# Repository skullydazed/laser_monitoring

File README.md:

Device For Monitoring Some Critical Parameters of a CO2 Laser Cutter.
=====================================================================

This is a project undertaken by members of Idea Fab Labs in Santa Cruz to
help monitor some critical parameters of our laser cutter. We're using
this to monitor 6 different parameters on our Redsail 100w Laser Cutter:

* Overall AC current usage (as measured at the electrical panel's "In")
* Chiller AC current usage
* AC in to power supply
* DC out of power supply
* Temperature at the tube's water inlet
* Temperature at the tube's water outlet

Who Built This?
---------------

This project was created by [Zach White](https://github.com/skullydazed) with
significant contributions from Ben Hencke ([github](https://github.com/simap),
[website](http://www.bhencke.com)), Austin Neff, and Chris Maddox.
Many other members at Idea Fab Labs contributed ideas and suggestions in
the process of building this.

Special thanks to Kelsey Rice, the Laser Zone Manager, for being open to this
crazy idea and lending his support.

Repository Contents
===================

Arduino Shield
--------------

* [doc/Arduino Shield Gerbers](doc/Arduino Shield Gerbers) - This directory
  contains gerbers for the Arduino Shield.
* [doc/Arduino Shield Schematic.png](doc/Arduino Shield Schematic.png) - The
  schematic for hooking up the sensors to the Arduino.
* [CAD/Laser Monitor.brd](Laser Monitor.brd) and
  [CAD/Laser Monitor.sch](Laser Monitor.sch) - EAGLE files for the Arduino
  Shield

Raspberry Pi
------------

* [CAD/Laser Cut Case.dxf](CAD/Laser Cut Case.dxf) - Plans for a case that
  can contain the Raspberry Pi

Software
--------

* [Laser_Monitoring.ino](Laser_Monitoring.ino) - Arduino sketch for reading
  and reporting data over serial
* [laserd](laserd) - Python 3.4 script to fetch readings and shove
  them into an RRD
* [laser_lcd](laser_lcd) - Python 3.4 script to fetch readings from RRD and
  display them on a PiFace Control and Display board

Required Parts
==============

* 1 &times; Computer with USB able to run python 3.4
* 1 &times; [Arduino](http://store-usa.arduino.cc/products/a000066) (we used
  an Uno, but any arduino with analog pins will work.)
* 3 &times; [50A Current sensors](http://www.robotshop.com/en/dfrobot-50a-current-sensor-ac-dc.html)
* 2 &times; [LM34DZ Fahrenheit Temperature Sensor](http://www.allelectronics.com/make-a-store/item/lm34dz/fahrenheit-temperature-sensor/1.html)

Optional Parts
--------------

These parts aren't required for the monitoring portion, but we found each one
to be a valuable addition to our implementation.

* 1 &times; [Raspberry Pi](https://www.raspberrypi.org)
* 1 &times; [PiFace Control and Display Board](https://www.element14.com/community/docs/DOC-55622/l/piface-control-and-display-board-for-use-with-raspberry-pi)
* 1 &times; USB Wifi Adaptor
* 1 &times; [Custom Arduino Shield](Laser Monitor.brd) - etch it yourself or
  have it made
* 6 &times; 10k resistors
* 1 &times; [Varistor](http://www.mouser.com/search/ProductDetail.aspx?R=0virtualkey0virtualkeyV8ZA2P) for overload protection
* 1 &times; Laser cut case. See [Laser Cut Case.dxf](Laser Cut Case.dxf) for
  plans. Use any 3mm (1/8") material.
* 24 &times; M3 x 10 Screw + Nut

Assembly
========

Program The Arduino
-------------------

(You can do this part on any computer, it doesn't have to be the monitoring
computer.)

1. Open the [Laser_Monitoring.ino](Laser_Monitoring.ino) file in the Arduino
   IDE
2. Upload the sketch to the Arduino
3. Open up the Serial Monitor (Tools -> Serial Monitor)
4. You should see a line written once a second consisting of 6 tab separated
   numbers
5. Close the Arduino IDE

Wiring
------

Start by wiring up your Arduino. If you have made the PCB, you only need to
plug the current sensors in, wire up the temp sensors, and interface with the
laser's power supply for DC current. If you decide to forego the PCB you
will need to reference [the schematic](doc/Arduino Shield Schematic.png) to get
everything wired up properly.

You will need to make your own pigtails for the temperature sensors. For
consistency with the current sensors we recommend using Red for VCC, Blue for
Signal, and Black for GND.

FIXME: Have Ben describe connecting the DC current sensing.

Once you've wired up the Arduino, you can plug it into the monitoring computer
(in our setup that's the Raspberry Pi)

Setup and First Run
===================

* Clone this repository to /home/pi/Laser_Monitor
* Create the RRD file:
  * `rrdtool create readings.rrd --step 1 \`  
    `DS:current1:GAUGE:30:U:U \`  
    `DS:current2:GAUGE:30:U:U \`  
    `DS:current3:GAUGE:30:U:U \`  
    `DS:dc_current:GAUGE:30:U:U \`  
    `DS:temp1:GAUGE:30:U:U \`  
    `DS:temp2:GAUGE:30:U:U \`  
    `RRA:AVERAGE:0.5:1:24 RRA:AVERAGE:0.5:6:10`
* Run `laserd` to read data from the Arduino and write it to an RRD file.
* Run `laser_lcd` to read data from the RRD and write it to the LCD.

Systemd
=======

If you're using a systemd based distribution you can use
[setup_systemd.sh](setup_systemd.sh) to setup the RRD file and the services
that will write to and read from that RRD.

TODO
====

* Create a web interface to display data from the RRD

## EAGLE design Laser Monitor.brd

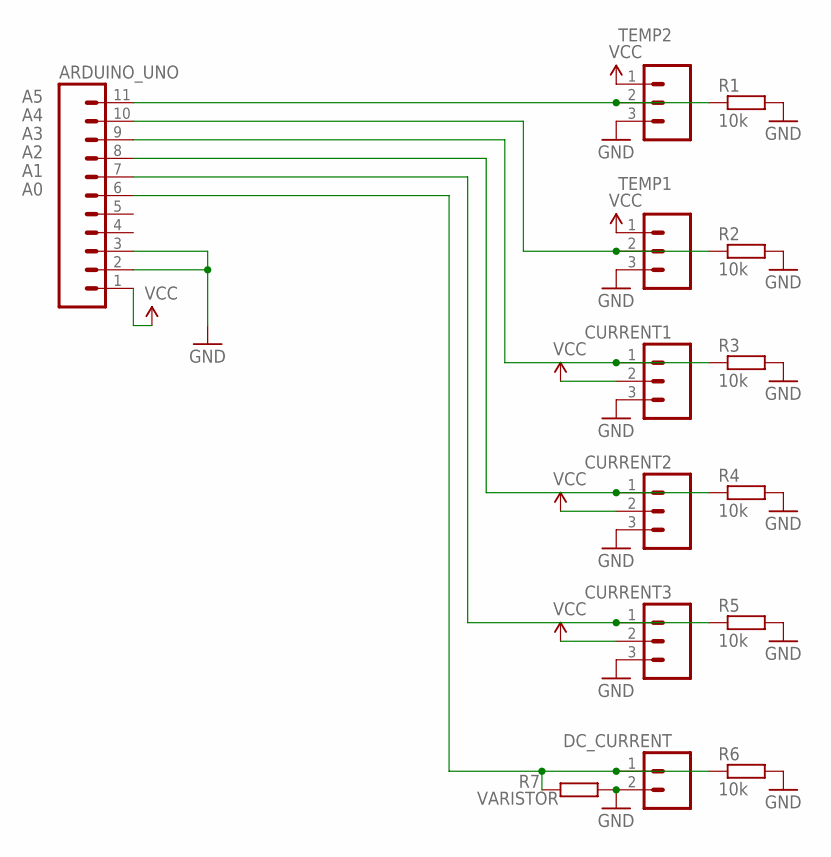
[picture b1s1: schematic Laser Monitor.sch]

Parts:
ARDUINO_UNO: M11PTH; 1X11
CURRENT1, CURRENT2, CURRENT3: M03PTH; 1X03
DC_CURRENT: M02PTH; 1X02
R1, R2, R3, R4, R5, R6: 10k; 0204V
R7: VARISTOR; P0817V
TEMP1, TEMP2: M03PTH; 1X03

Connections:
A0: ARDUINO_UNO.6, DC_CURRENT.1, R6.1, R7.2
A1: ARDUINO_UNO.7, CURRENT3.1, R5.1
A2: ARDUINO_UNO.8, CURRENT2.1, R4.1
A3: ARDUINO_UNO.9, CURRENT1.1, R3.1
A4: ARDUINO_UNO.10, R2.1, TEMP1.2
A5: ARDUINO_UNO.11, R1.1, TEMP2.2
GND: ARDUINO_UNO.2, ARDUINO_UNO.3, CURRENT1.3, CURRENT2.3, CURRENT3.3, DC_CURRENT.2, R1.2, R2.2, R3.2, R4.2, R5.2, R6.2, R7.1, TEMP1.3, TEMP2.3
VCC: ARDUINO_UNO.1, CURRENT1.2, CURRENT2.2, CURRENT3.2, TEMP1.1, TEMP2.1

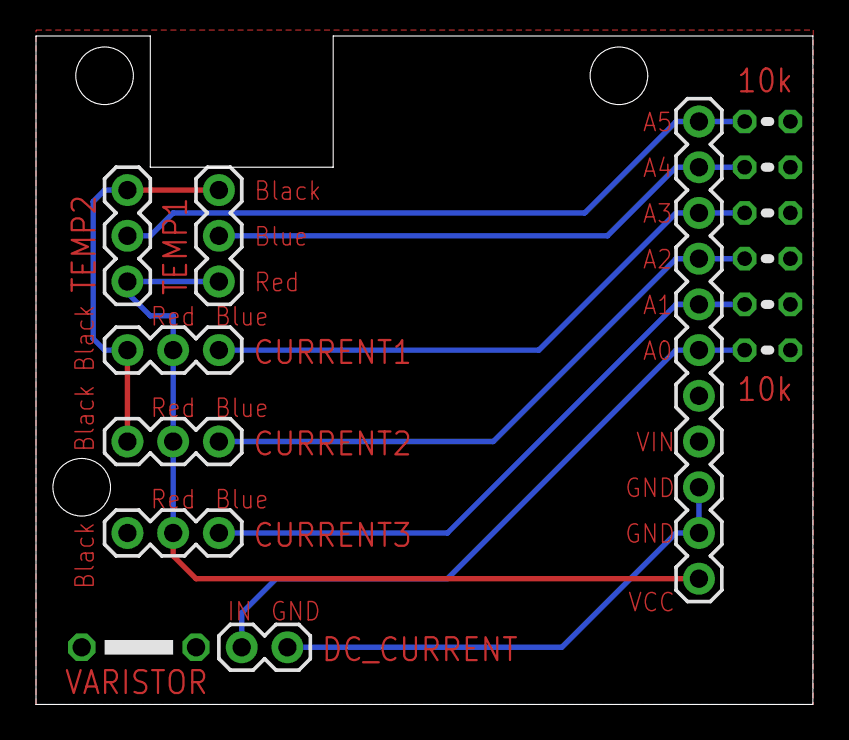
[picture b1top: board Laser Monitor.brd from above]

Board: 2 copper layers, 43.2 x 37.1 mm, 14 parts (0 on the bottom side), 8 nets.

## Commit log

2016-06-25 Update the README to link to Ben's github and website
2016-06-26 Add the laserd and laser_lcd services
2016-06-26 Fixing formatting

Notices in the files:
parts and their libraries:
SparkFun-Connectors: Licensing: Creative Commons ShareAlike 4.0 International - https://creativecommons.org/licenses/by-sa/4.0
